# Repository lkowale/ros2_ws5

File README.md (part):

# ros2_ws5

## Sliding toolbar — software

All toolbar code lives here (ros2_ws5). It runs in the Gazebo sim and, for testing,
on the physical **solbot4** robot (pd600) as an overlay on `~/ros2_ws4`. Do not copy
it into ros2_ws4; change it here and redeploy.

| Package | What |
|---|---|
| `toolbar` | `toolbar_service`: executes toolbar moves, enforces soft limits, monitors the actuator, reports to PauseManager. `firmware` param: `solbot_main` (solbot5 board, metres) or `main_esp32_pio` (solbot4 board, ADC counts). Config: `config/toolbar_solbot5.yaml` |
| `toolbar_msgs` | `ToolbarState.msg` (`/toolbar/state`, 10 Hz), `ToolbarControl.srv` (`/toolbar_control`) |
| `solbot4_toolbar` | solbot4 launch (`core_toolbar.launch.py` = ws4 `pd600_core.launch.py` + `toolbar_service`) and calibration (`config/toolbar.yaml`) |
| `tool_slider` | `tool_slider_controller` (row offset → `/tool_bar_position_cmd`, PID), sim actuator + plant-row sim |
| `crop_row_vision` | camera crop-row detection → `/plant_row_offset` |

Interface (metres from centre, +right): `toolbar_service` follows `/tool_bar_position_cmd`
in `auto` mode and publishes the measured `/tool_bar_position`, the same topics
`tool_actuator_sim` uses in the sim. Commands: `set_position`, `center`, `hold`, `auto`,
`enable`, `disable`, `reset_fault`, `get_status` (service `/toolbar_control` or
topic `/toolbar/cmd`). Starts **monitor only** (`actuator_enabled: false`). A disabled
toolbar never pauses the robot.

### Running on solbot4 from the laptop

```bash
bash pd600.sh deploy                # rsync toolbar packages to pd600:~/ros2_ws5, build there on ws4
bash pd600.sh start_bar             # all-in-one: core + toolbar + OAK-D + bar_follower (one tmux)
bash pd600.sh start                 # core stack (run_core_um982.sh, field_nav_hw params) + toolbar, tmux "solbot4"
bash pd600.sh attach                # watch (Ctrl-b d detach, Ctrl-c stop)
bash pd600.sh state                 # one /toolbar/state (raw_position = TPS counts)
bash pd600.sh toolbar enable        # set_position 0.02 | center | hold | auto | reset_fault | disable
bash pd600.sh stop | status
bash pd600.sh ros2 <args...>        # any ros2 command on the robot
bash pd600.sh camera                # OAK-D (solbot4_toolbar/oakd.launch.py, RGB 1280x720 @10 fps) + JPEG
                                    #   domain_bridge 0→1 to hp-zbook, tmux "oakd"; start AFTER `start`
bash pd600.sh view                  # laptop: oakd_view.py (OpenCV window, Hz/kB overlay) of /oakd/rgb/image_raw/compressed, domain 1
bash pd600.sh camera_stop
bash pd600.sh gui                   # laptop: toolbar_gui.py — slider (target sent on release), Enable/Disable/
                                    #   Centre/Auto/Reset fault/HOLD, live state; ssh pipe to toolbar_gui_remote.py, no DDS
```

Requirements on pd600: `~/ros2_ws4` on branch `feature/toolbar-service` (adds the
`CORE_PKG` / `CORE_LAUNCH` / `OVERLAY_SETUP` hook to `run_core_um982.sh`).
`pd600:~/ros2_ws5` is build-only: `deploy` overwrites it, and the deployed version is in `DEPLOYED`.

Gotchas:
- ws4's `run_core*.sh` begin with `pkill -9 -f "ros2|..."`, which kills **any** process with "ros2" in its
  command line, `ros2_ws5` paths included. `pd600.sh start` avoids this. If you start by hand, use
  `cd ~/ros2_ws5 && bash run_solbot4_toolbar.sh` from an interactive shell.
- After removing messages from a rosidl package, rebuild it clean (`rm -rf build/<pkg> install/<pkg>`),
  otherwise typesupport fails to import.
- solbot4 firmware (`main_esp32_pio`) has no goal clamp and no stall, overcurrent or comm-timeout
  protection. The node's limits and jam check are the only guard.

### Status / TODO
- [ ] solbot_main v2 rev C (5 V sensors, ADS1115 module on 5 V): review the new routing in KiCad, check
  Q5/Q6/C24/R35/R40 in JLC's placement preview, order. Confirm the module pin order matches the board labels.

- [x] pd600 ESP32 (`ESP32_solbot_main`, DHCP on `solap`: was .101/.104/.102, **192.168.0.106** on 2026-11-11) runs
  `main_esp32_pio` ws4 (uncommitted: PV hold + per-target drive timer + toolbar min PWM 100), OTA-flashed 2026-11-11.
  The laptop can't reach it; build here, relay through pd600 and resolve the IP there:
  `pio run -e esp32dev_ota` (in `~/ros2_ws4/embedded/main_esp32_pio`), `scp .pio/build/esp32dev_ota/firmware.bin
  ~/.platformio/packages/framework-arduinoespressif32/tools/espota.py pd600:/tmp/`, then
  `ssh pd600 'python3 /tmp/espota.py -i $(getent hosts ESP32_solbot_main.local | cut -d" " -f1) -f /tmp/firmware.bin'`
- [x] Firmware safeguards in `main_esp32_pio` (ws4): toolbar idle until the first `toolbar/set_position`, stall
  (1.5 s, ≤3 counts) and max-drive-time (20 s) trips, `TPS_fault` / `TPS_active` in `ads`. Built, host unit-tested.
  - [x] goal clamp 370..1280 (~4 mm inside the ends), max drive 10 s. OTA-flashed 2026-11-05
- [x] Actuator moves (2nd test 2026-11-05; 1st test had no movement and tripped stall)
- [x] PV SSR 60 s min on/off hold + 42 V hard cut-off in `main_esp32_pio`: OTA-flashed 2026-11-07
  - [ ] commit in ws4; compare the next day's `~/ros2_ws4/logs/pv_ssr/` with 2026-11-07 (up to 58 switches/h)
- [x] Toolbar max-drive timeout (10 s) now counts per target: a goal change > 3 counts restarts it (stall check
  unchanged). OTA-flashed 2026-11-07 together with the PV hold
- [ ] Node: on a firmware-reported fault, `_latch` sends a hold goal, which re-arms the firmware (`TPS_active` true).
  It should leave the firmware idle
- [x] Direction correct, no change needed (`CW`): +right → TPS falls, −left → TPS rises. Both IBT-2 inputs work
- [x] Calibrated: TPS **1300 far left, 350 far right**, toolbar travel **±0.10 m** (200 mm; actuator stroke
  100 mm at 15 mm/s, full stroke ~6.7 s) → 4.75 counts/mm, counts fall going right. Centre 825 counts
- [x] Wire the actuator, `toolbar enable` (holds at the current position, clamped into 370..1280), small `set_position` moves
- [x] IBT-2 pins: GPIO26 RPWM / GPIO27 LPWM (confirmed 2026-11-05)
- [ ] **IMPORTANT — motion interlock:** lift **down** → toolbar may only move while the robot is moving
  (tool in the soil, sliding sideways while stationary would gouge/strain it); lift **up** → always allowed.
  Needs lift state + robot speed in the node (and ideally a firmware-side guard too)
- [x] Laptop slider GUI (`bash pd600.sh gui`)
- [ ] Phone slider via HiveMQ (`outer/toolbar_pos`, `toolbar_outer_bridge`) — running on pd600, get_status round trip via HiveMQ OK; slider move not yet tested
- [ ] Vision loop on solbot4: deploy `tool_slider` + `crop_row_vision` (`PKGS=... bash pd600.sh deploy`), camera topic on solbot4

## Tool slider actuator — IBT-2 on the old main ESP32 board

The sliding toolbar actuator is driven by an IBT-2 (BTS7960) plugged into one of
the spare IBT-2 ports on the old classic-ESP32 main board.

Sources:
- Old wheel firmware (defines the IBT-2 ports): `~/tmp/solbot_arduino/solbot2-2x12vwipersmotors/esp32_master____wheels_diff*`
- Firmware currently on the board: `~/ros2_ws4/embedded/main_esp32_pio` (earlier `main_esp32`)

### Old IBT-2 ports vs current pin usage

| Port (solbot2)   | RPWM | LPWM | Current use (main_esp32_pio)                         |
|------------------|------|------|------------------------------------------------------|
| Front-left wheel | 32   | 33   | taken: steering_act (LEDC ch 0/1)                    |
| Front-right wheel| 25   | 26   | 25 taken: `PV_SWITCH_PIN`; **26 = toolbar RPWM**     |
| Rear-left wheel  | 23   | 22   | 22 taken: I2C SCL (BNO08x + ADS1115, default Wire)   |
| Rear-right wheel | 27   | 13   | **27 = toolbar LPWM**; 13 free                       |
| Lifter           | 19   | 21   | 21 taken: I2C SDA                                    |
| Planter          | 18   | 17   | taken: lift_act (LEDC ch 2/3)                        |
| LAS analog in    | 35   | –    | free (input-only ADC)                                |

Also in use: GPIO34 = steering pot ADC.

### Assignment for the slider

Used (confirmed 2026-11-05), as in ws4 `main_esp32_pio` since `ee2e8b7`:

- RPWM = **GPIO26**, LPWM = **GPIO27**. Neither is a strapping pin.
- LEDC channels **4 / 5** (5 kHz, 8-bit, same as `IBT_2.cpp`)
- Position sensor (TPS): **ADS1115 AIN2** (`TOOLBAR_ADS_CH 2`), published as `TPS` in the `ads` topic

```cpp
#define TOOLBAR_RPWM_PIN 26
#define TOOLBAR_LPWM_PIN 27
#define TOOLBAR_ADS_CH   2
toolbar_act.begin(0, "toolbar_act", TOOLBAR_RPWM_PIN, TOOLBAR_LPWM_PIN, 4, 5, Lin_act_pid::CW);
```

(An earlier plan used RPWM 27 / LPWM 13, the old rear-right wheel port. Not used.)

## WAS (wheel angle sensor) — salvaged BMW position sensor

Under test (2026-10-30) on an ESP32 DevKit V1. Range is about 90°.

| Sensor pin | Function |
|------------|----------|
| 1          | GND      |
| 4          | Signal   |
| 5          | +5 V     |

Pins 2 and 3: unknown / not used.

The sensor runs on 5 V, so its output may go above 3.3 V. Measure the signal
range with a meter before connecting it to an ESP32 ADC pin, and use a divider
(e.g. 10k/20k) if it exceeds ~3.1 V.

## Changelog

Newest first. Toolbar and solbot4-test work. Add an entry with every change.

### 2026-11-11
- **bar_follower `reference: markers` (new default): two knives, one each side of the crop row, each with a
  yellow marker; keep the red bar midway between the markers.** Visual servo on the image, no knife model:
  markers (yellow H 18-45, S>50, V>130, compact 400-4000 px blobs, rows of the measuring tape rejected) ->
  midpoint; bar centreline at the markers' row; `err = u_bar + center_offset_mm·2.62 - u_mid`. Only after the
  toolbar reached its target and was still `settle_s` 0.6 s: median of `settle_frames` 3 errors, if over
  `deadband_mm` (now 3) -> `target = p + err / gain(p)`, gain = `px_per_m + 2·px_per_m2·p` (new `px_per_m2`
  −2867 from the 11-10 sweep). Joint play / scale errors are taken out by the next iteration. One marker
  hidden: the other ± the remembered spacing. Markers or bar lost 0.5 s -> stop commanding (service holds).
  Clamped to the service limits (asymmetric since the zero move). `reference: model` keeps the 11-07 mode.
- Bar detection: tallest red component + pieces on its line (was: all red pieces merged), `red_v_min` 40 -> 75,
  and in markers mode only columns within one marker spacing of the knives. The rusty frame at the left image
  edge (V 43-62) was passing as the bar (u ≈ 18 px).
- Live test markers mode: bar 9 mm off -> −0.8 mm in 2 moves; chasing the bar to the left end the target hit
  −77.4 mm, but the firmware clamps goals at TPS 1280 (−75.2 mm), so the toolbar stayed "moving" until
  `arrive_timeout_s`. Follower clamp now 5 mm inside the service limits (was 2). After the fix: reversal from
  the left end +27 -> +17.6 (joint play ate half the first step) -> +4.1 -> +0.6 mm.
- **bar_follower `reference: knives` (new default): the knives themselves at ground level, not the markers.**
  The yellow markers sit 5-10 cm above the ground, and their parallax put the "centred" bar 22 mm off the
  knives' real midpoint. Inner wing tip of each knife = extreme of the blue-steel mask on its side of the bar
  centreline (left knife max u+v, right knife max v-u, mean of the 30 most extreme px), rows from the tape
  top down ignored (tape and the shank bolt look bluish), blobs < `knife_min_blob_px` 1500 ignored (a bluish
  dirt spot next to the left tip was taken as the tip now and then, error jumping ~6 mm), tips = median of
  the last 3 frames. Stationary noise: sd 1.8 mm with outliers to −6 -> 0.28 mm, range 0.3-1.7 mm.
- Continuous servo hysteresis: start correcting above `deadband_mm` (3), stop updating the target below
  `release_frac`·deadband (1.5 mm) or when at rest inside the deadband. Without it the loop dithered back and
  forth through the implement joint play (near the target small actuator moves don't move the knives).
  After both fixes: target unchanged for 18 s with a still bar, error 0.1-0.3 mm.
- **bar_follower `servo: continuous` (new default for markers mode):** the stepped loop (move, wait for the
  target + 0.6 s + 3 frames, measure, move) made the toolbar visibly stop-and-go behind a moving bar. Now every
  frame: `target = p(t_image) + servo_gain(0.8) * err / gain(p)`, `p(t_image)` interpolated from the
  /toolbar/state history at the image header stamp (pd600 clock), resent only when it changes > 0.5 mm; held
  when still and |err| <= deadband. `servo: stepped` keeps the old loop. Live: 44-50 mm bar moves followed in one
  smooth motion, converged −0.4..+0.8 mm in 2.7-9.3 s, no stalls.
- **Firmware `TOOLBAR_MIN_PWM` 100 (ws4 `main_esp32_pio`, uncommitted, OTA-flashed 2026-11-11 to .106):**
  `Lin_act_pid::min_pwm` (default 40, steering/lift unchanged) is the bottom of `calculate_pwm`'s 5..100-count
  ramp. A 3.5 mm (17-count) follower step got PWM ~75/255, didn't move with the knives on concrete, and tripped
  `stall` after 1.5 s (latched until reset_fault + auto). After the flash: four 3 mm (12-count) steps both ways
  reached the target, no stall.
- pd600 rebooted again 2026-11-11 and the OAK-D was missing from `lsusb` until replugged (same as 11-10).

### 2026-11-10
- **Toolbar zero re-referenced to the bar's working centre (TPS 923, was 825 = mid-stroke).**
  `config/toolbar.yaml`: same counts at the ends (1300 left, 350 right, 4.75 counts/mm), limits now
  `min_position -0.0794` / `max_position +0.1206`; `center` command and 0 m go to TPS 923. Verified on
  pd600 after deploy + restart: raw 923 reads 0.000 m. toolbar_gui picks the new limits up from `/toolbar/state`.
- **`toolbar_cam.yaml` u0 1071.7 -> 1011.7** for the new zero (u0 − 2907·0.0206). Camera check of the sweep:
  max left (raw 1277) knife ≈800 px vs 815 predicted, back to centre ≈1035 vs 1032. Against the tape the knife moves
  ~1.1–1.18 mm per configured TPS mm (−88 mm at −74.6, +66 at +60.8), consistent with the 11-07 px_per_m (1.11).
- Bar-follower test re-run with `start_bar`: bar at u 788 px, follower live (enable, auto, dry_run false) settled
  at −0.056 m with err −0.7 mm.
- **Follower accuracy sweep** (`measure_knife_bar.py` on pd600: after each settle, knife bottom-left corner
  (blue-steel mask; the 11-07 V<95 mask misses the lit wing) vs red-bar centreline at that row, 2.62 px/mm;
  data + annotated frames in `docs/toolbar_cam_calib/follow_check_2026-11-10/`). Goal offset 30 mm, 13 steps:
  arriving from the right (−p) 29.3–31.7 mm; arriving from the left (+p) 27.3 mm at −46 mm, 24–26 mm around
  0, 21.5 at +43, 14.5 at +90 (+94.5 saturated at `limit_m`). The follower's own err stayed within ±2 mm, so the
  error is the camera model. Fit of knife u vs p (new frame): linear `999 + 2644·p ± 39/2` leaves 6.4 px rms
  (10 px max, curved residuals); quadratic `1009.6 + 2788·p − 2867·p² − 47.8/2·dir` leaves 2.3 px rms (3.8 max,
  < 1.5 mm). Local scale falls from 3130 px/m at −0.06 to 2270 at +0.09 (lens edge + linkage).
  The 11-07 linear model (2907 px/m) was fitted on −0.10…−0.01 m (new frame) only. TODO: quadratic in bar_follower.
- OAK-D on pd600 enumerated at 5 Gbps (USB SPEED: SUPER) on bus 2 port 10. pd600 rebooted once
  unexpectedly with the camera attached: watch for a USB power brown-out.

### 2026-11-09
- **solbot_main v2 rev C: 5 V position sensors and an optional ADS1115 module on 5 V, as on the ws4 toolbar.**
  Hall sensors: POS terminal pin 1 = +5V through a 0 R link (direct, as ws4). The output goes to the ESP ADC through 100k/150k (×0.6, 5 V → 3.0 V) + 100 n +
  BAV99. The ADS1115 breakout module sits in a 1x10 socket (J15), lying flat below the SPARE IDC. It is powered from
  +5V and reads the raw 0..5 V wipers (PGA ±6.144 V, I2C 0x48); SDA/SCL pass 2× 2N7002 level shifters (Q5/Q6) so its
  5 V pull-ups don't reach the ESP. R35/R40 moved above the TURN terminal (their old spots were boxed in).
  Routing: rev B copper locked; segments on re-netted pads dropped, dead stubs pruned (`gen_pcb.py`), new connections
  by FreeRouting (pass4) + `gen/route_net.py` (pass5, 2 nets). Only the nets this change touches differ from rev B.
  DRC: 0 unconnected, no clearance errors. Production: BOM 27 lines (new Basic 0 R C21189, 150k C22807; 1M gone),
  99 placed parts. Firmware: `pot_mv` = sensor supply (default 5000, NVS key `pot_mv5`), ESP reading ÷ `pins::POS_DIV`,
  ADS gain ±6.144 V, ADS auto-detect with fallback to the ESP ADC (`settings {"pos_adc":"auto|esp|ads"}`), channel map
  `pins::ADS_CH`. Builds and the host tests pass; not run on hardware.
- **solbot_main v2 firmware (solbot5): ported the ws4 toolbar and PV changes.** The slider (act 3) now starts idle
  until the first `slider/set_position`. It trips `timeout` after 10 s driving towards one target; a goal change of more
  than `stall_delta` restarts that clock. Soft limits come from the solbot4 measurements (counts 370..1280 = ±0.0958 m;
  calibrate on solbot5). PV: 60 s minimum on and off hold, 42 V immediate cut-off in any mode. `ads` adds `TBS_pwm`,
  `TBS_fault`, `TBS_active`; `act/state` adds `active`. Payloads that aren't JSON are ignored (they used to read as goal 0).
  Host tests extended, all pass; firmware builds. Not run on hardware (board not built yet).
- **Removed `embedded/solbot_main` (v1 board)**; v2 is the only solbot5 controller. v1 is in git history before this commit.

### 2026-11-07
- **Firmware: toolbar timeout per target** (ws4 `Lin_act_pid::command()`, flashed with the PV hold change). The
  follower tripped `ESP32 reports toolbar actuator timeout` at 13:28: the target kept moving with the bar, the motor
  never stopped, and the 10 s continuous-drive limit ran out. Now a new goal (> `stall_delta` = 3 counts, so the
  node's periodic resends don't count) restarts the 10 s clock; the stall reference is not reset, so a jammed
  actuator still trips after 1.5 s. After the flash: reset_fault / enable / auto, follower at target (−0.7 mm).
  OTA: the ESP32 had moved to 192.168.0.102 (DHCP); resolve `ESP32_solbot_main.local` on pd600.
- **PV SSR hold (firmware, not flashed):** `main_esp32_pio` (ws4) PV switch keeps each state >= 60 s
  (`PV_MIN_HOLD_MS`) and still cuts PV at once above 42 V (`PV_HARD_OFF_VOLTAGE`). Reason: on 2026-11-07, with the
  41/40 V thresholds, PV switched up to 58 times an hour, with 1-3 s bounces after reconnects.
- **One-session startup for the bar-follower test:** `bash pd600.sh start_bar [launch args]` ->
  `run_solbot4_bar_follower.sh` -> ws4 `run_core_um982.sh` with `CORE_LAUNCH=core_bar_follower.launch.py`
  (`solbot4_toolbar/launch/`): core_toolbar (pd600_core + toolbar_service + toolbar_outer_bridge) + OAK-D +
  camera domain_bridge (`CAMERA_BRIDGE_CYCLONEDDS_URI`) + bar_follower. Args `use_camera`, `use_bar_follower`,
  `camera_model`, `bar_follower_params`. Replaces `start` + `camera` + `follow` (start_bar refuses if those
  sessions run); `stop` handles both launches. Toolbar still starts disabled, follower in dry_run.
- **`bar_follower`** (`solbot4_toolbar/scripts/bar_follower.py`, params in `config/toolbar_cam.yaml`): keeps the knife's
  left edge `offset_mm` (30) right of a red bar/cable. Red mask -> per-row edge midpoints -> line fit -> bar column at
  v_ref; target `p = (u_bar + offset·2.62 px/mm - u0 ∓ hysteresis/2) / px_per_m`, approach-direction aware, 5 mm
  deadband, published on `/tool_bar_position_cmd` (no PID: the camera is frame-fixed, the firmware closes the loop).
  Bar lost 0.5 s -> stops publishing, `toolbar_service` holds. Starts `dry_run: true`. Status JSON
  `/bar_follower/status`, overlay `/bar_follower/image/compressed` (bridged to the laptop).
  `pd600.sh follow | follow_stop | follow_view`, `view [topic]`. Static check: bar 795 px, toolbar −0.0236 ->
  target −0.075 m; the TPS prediction matched the detected knife corner within 7 px (~3 mm).
- **OAK-D <-> toolbar calibration** (`solbot4_toolbar/config/toolbar_cam.yaml`, data and frames in
  `docs/toolbar_cam_calib/`): lift down, tape on the floor, toolbar swept ±0.08 m, knife bottom-left corner
  auto-detected. `u_impl = 1071.7 + 2907·p ± 20 px` (px, p in m, +p = image right; knife visible only for p <= ~+0.01).
  Ground scale 26.2 px/cm, so the knife moves 1.11 mm per TPS mm (TPS travel scale or knife pivoting).
  **Hysteresis ~40 px = ~15 mm** between approach directions (repeatable to 1 px per direction): implement joint play.
- `toolbar_gui.py` + `toolbar_gui_remote.py`, `bash pd600.sh gui`: tkinter slider GUI on the laptop. The robot graph is
  loopback-only, so the GUI copies `toolbar_gui_remote.py` to pd600 and runs it over ssh (JSON lines: `/toolbar/state`
  out, `/toolbar_control` requests in). Slider sends `set_position` on release; ←/→ ±5 mm (Shift ±1 mm), `c` centre,
  space HOLD; closing the window sends hold if enabled. `deploy` also copies the remote helper.
- `toolbar_outer_bridge` (package `toolbar`, started by `core_toolbar.launch.py`): phone MQTT app via the HiveMQ cloud
  broker, same pattern as ws4 `mqtt_op` outer/steer + outer/speed. `outer/toolbar_pos` `{"data": mm}` (−100..100,
  +right) → `toolbar_control set_position`; `outer/toolbar_cmd` `{"data": "enable"|"center"|"hold"|…}`; replies on
  `outer/toolbar_state` `{pos_mm, target_mm, state, ok, message}`. Coalesces slider bursts (newest value, one call in flight).

### 2026-11-06
- OAK-D on solbot4: `solbot4_toolbar/launch/oakd.launch.py` + `config/oakd.yaml` (depthai_ros_driver, RGB only,
  720p 10 fps, `CAMERA_MODEL` default OAK-D-LITE), `config/camera_bridge.yaml`, `run_solbot4_camera.sh`;
  `pd600.sh camera | camera_stop | view`. `pd600.sh stop` now waits for `core_toolbar.launch.py` only.
  First run: OAK-D-LITE (MXID 19443010A18FDC7D00) on the pd600 front USB-C, USB3 SUPER_PLUS after a replug
  (first plug-in: no Type-C partner detected). 10 Hz on pd600, only ~3 Hz arriving on hp-zbook over Tailscale.
  Replugging re-enumerated the UM982 CH340 (`/dev/um982` → ttyUSB1); GPS kept running.
  JPEG q95 (426 kB frames, ~4 MB/s) saturated the solap WiFi once the laptop joined it (LAN ping 460 ms, viewer
  stalled): `oakd.yaml` sets jpeg_quality 50 (~140 kB, ping 1.5 ms, 8 Hz on the laptop), bridge image QoS best effort.
  `view` runs `oakd_view.py` (rqt_image_view / image_view never subscribed to the bridged compressed topic), under `env -i` (rqt crashed in the VS Code snap shell: GLib-GIO settings schema).
- OAK-D ground footprint (1280x720, fx 912), tape measures on flat concrete:

  | Lift | Camera height (measured) | Ground window | Scale | Optical-equivalent height |
  |---|---|---|---|---|
  | down | 44 cm | 55 × 31 cm, rectangular | 23.2 px/cm (0.43 mm/px), uniform | ~39 cm |
  | up | 64 cm | ~79 × 50 cm, trapezoid | 17.8 (top) → 15.5 (mid) → 12.5 (bottom) px/cm | ~59 cm |

  Lift up the camera pitches (bottom of the image looks farther away) and the lift frame hides the right ~15 %.
  The measured heights are ~5 cm above the optical-equivalent height (measured to the mount, not the lens).
  Lift down is a clean nadir view; lift up needs a tilt/homography correction before metric use.
  Frames: `docs/oakd_ground/lift_down_44cm.jpg`, `docs/oakd_ground/lift_up_64cm.jpg`.
- TODO added: toolbar motion interlock — lift down ⇒ move only while driving; lift up ⇒ always allowed.

### 2026-11-05
- **Toolbar moves, direction correct** (2nd powered test, standalone node, no robot stack):
  `set_position −0.023` (10 mm right): TPS 983 → 937 in ~0.9 s, goal 934 (3 counts ≈ 0.6 mm off, inside the
  firmware deadband), `at_target`. Back to `−0.033` (10 mm left): TPS 937 → 979 in ~1 s, goal 982. No faults.
  `CW` in firmware is correct.
- **First powered toolbar test** (standalone `toolbar_service` on pd600, no robot stack): enable held at TPS 983
  (−0.033 m). `set_position −0.023` (goal 934) drove PWM ~142 for 1.5 s, but TPS stayed at 982–983. The firmware
  tripped `stall`, the node latched `actuator_fault`. **No movement, so the direction is still unknown.**
  The safeguards worked as designed.
- **Toolbar travel corrected to ±0.10 m** (200 mm toolbar travel from the 100 mm actuator stroke): node limits
  ±0.10 m, 4.75 counts/mm. Firmware clamp and timers are unchanged (counts/seconds), comments only, no reflash.
- **Toolbar calibrated and firmware flashed:** TPS 1300 left / 350 right, actuator 100 mm stroke, 15 mm/s.
  `solbot4_toolbar/config/toolbar.yaml`: ±0.050 m (corrected to ±0.10 m, see above), counts 1300/350,
  tolerances 2 mm and jam 5 mm.
  Firmware: clamp 370..1280, max drive 10 s. OTA-flashed: boots idle (`TPS_active` false, PWM 0). Before the flash,
  the old firmware was again driving PWM 250 (goal 1313, TPS 495, after the toolbar was moved by hand to measure).
  Deployed to pd600.
- **Firmware toolbar safeguards** (ws4 `main_esp32_pio`, `Lin_act_pid::enable_safeguards`, opt-in, so steering and lift
  are unchanged): idle at boot until the first command, goal clamp, stall trip (driving, ≤3 counts of movement in
  1.5 s) and timeout trip (driving > 20 s). Trips stop the motor and set goal := position, and a new
  `toolbar/set_position` re-arms. Null or invalid `data` is ignored, where before it read as goal 0. Motor is stopped
  when exactly on target (the old code kept the previous PWM). `ads` gains `TPS_fault` and `TPS_active`.
  `toolbar_service` latches `TPS_fault` stall/timeout as `actuator_fault`. Not flashed yet: waiting for the
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
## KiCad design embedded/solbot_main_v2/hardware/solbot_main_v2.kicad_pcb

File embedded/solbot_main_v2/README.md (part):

# solbot_main v2 (rev B / rev C) — compact ESP32-S3 main controller, JLCPCB Basic parts

> **rev C (2026-11-09): production files regenerated and checked by script. Two manual checks
> are left before ordering** (see the end of this list).
> * **Hall position sensors on 5 V** (as on the ws4 toolbar): POS terminal pin 1 = +5V through a 0 R
>   link (R35/R40/R45/R50; fit 10–47 R there if you want a shorted cable not to pull +5V down, at the
>   cost of supply volts). The sensor output goes to the ESP ADC through a 100k/150k divider (5 V reads
>   as 3.0 V; an open wiper reads 0) + 100 n + BAV99 clamp. The rev B 1 k from 3V3A and the 1M
>   wiper pull-down are gone. R35/R40 (A1/A2 supply) moved to the free strip above the TURN
>   terminal: their old spots could only be reached through the 3V3A pull-up row.
> * A 1x10 socket (J15, hand-solder) for an optional **ADS1115 breakout module** plugged in flat,
>   **powered from +5V like on ws4** and reading the **raw 0..5 V wipers** (PGA ±6.144 V). SDA/SCL
>   reach it through two 2N7002 level shifters (Q5/Q6, gate 3V3A), so the module's own 10k pull-ups
>   to 5 V never reach the ESP pins. C24 = 100 n on its VDD.
> * Routing: the rev B copper is kept apart from the segments that ended on re-netted pads (dropped)
>   and the dead stubs this left (pruned at the end). Only the nets this change touches differ from
>   rev B. New connections: FreeRouting (`solbot_main_v2_pass4.ses`) + `gen/route_net.py` for the two
>   it couldn't close (`solbot_main_v2_pass5_*.ses`).
> * DRC: 0 unconnected, 0 clearance errors, 0 shorts. The other warnings are the same as rev B, plus
>   headless-only `lib_footprint_issues` for J15/C24/Q5/Q6.
> * `hardware/production/` was regenerated with the Fabrication Toolkit plugin (your saved
>   options). BOM: 27 lines, all with LCSC numbers. New: 0 R (C21189) and 150k (C22807), both Basic;
>   1M is gone; Q5/Q6 joined the 2N7002 line (C8545). Positions: 99 SMD parts. J15 is in neither file.
> * **Still to do by hand:** look over the new routing in KiCad (resistor block, around R35/R40
>   above the TURN terminal, under the ADS socket), and check Q5/Q6/C24/R35/R40 in JLC's placement
>   preview. Order as before: 2-layer, 1 oz. Upload
>   `production/solbot_main_v2.zip`, `production/bom.csv` and `production/positions.csv`.

The ESP32-S3 main controller for solbot5. It replaced v1 (a 190 × 155 mm board with a full
on-board 4-pack power path, removed from the repo 2026-11-09; see git history before that date).
This board has **no battery switching on board**. It

* runs from the robot's **12 V rail**
* **monitors the main battery bus voltage** (10S…20S, up to ~95 V) and its own 12 V rail
* switches **PV on/off through external DC solid-state relays** (2 driver outputs)
* drives **4 IBT-2 (BTS7960)** modules on **2×5 IDC sockets with the v3 pinout**, plus
  current sensing on the previously unused IDC pins 5/6
* reads the **4 position pots directly on the ESP32-S3 ADC1**, plus the **BNO085** on I2C

Board: **120 × 85 mm**, 2 layers, 1 oz is fine.

## JLCPCB assembly (rev B)

Every SMD part was checked on jlcpcb.com on 2026-10-16: **25 Basic lines and 1 Preferred
Extended (SMBJ18A TVS), 0 Extended**, so there are no extended-part fees with Economic
assembly.

**Production files: KiCad → Fabrication Toolkit (JLC plugin)** writes `hardware/production/`
(Gerber/drill zip, `bom.csv`, `positions.csv`). It's been checked against this board:
* Every connector is labelled on the silkscreen: function (TURN / LIFT / SLIDE / SPARE,
  12V IN, BUS SENSE, SSR1/2 PV, E-STOP, IMU) and pins (`+ W -`, `+ -`, `NC`, IMU pin names),
  plus an IBT-2 IDC pin legend at the top right.
* Every SMD footprint has an `LCSC` property (copied from the schematic field), so the
  plugin's BOM has all 26 lines with the right part numbers.
* Hand-soldered through-hole parts (12 V, BUS, SSR, E-stop and pot terminals, the IDC
  sockets, JST-XH, and the DevKit sockets) are "not in BOM" in the schematic and "exclude
  from BOM / position files" on the PCB, so they don't appear in either file.
* Keep the default options ("auto translate" on: rotation fixes for SOT-23/SOT-223/SOIC).
* In JLC's placement preview, check the polarity of D1/D3 (SS34), D2 (TVS) and the LEDs.
  The plugin has no rotation entry for D_SMA/D_SMB/LED footprints. If one is wrong, add an
  `FT Rotation Offset` field (e.g. 180) to that symbol.
* Don't rename the `LCSC` field or add a field called `JLC`/`MPN`: the plugin reads those as
  part numbers.

`hardware/bom_jlc.csv` (from `build.py`) is only a cross-check. Always order with the plugin's
`production/` files.

Changes from rev A that this required (none of the replaced parts is Basic):

| rev A (Extended) | rev B (Basic) |
|---|---|
| AP63205 buck + 4.7 µH inductor | 2× AMS1117-5.0 (logic / ESP32, like v3's 2× 7805), 2×22 Ω pre-drop on the ESP rail |
| AP2112K-3.3 | XC6206P332MR-G |
| ADS1115 | ESP32-S3 ADC1 (GPIO1–10 all used), 16× oversampled; rev B: pot top from 3.3 V through 1 k. Rev C: 5 V sensors, wiper ×0.6 divider, optional ADS1115 module back on a socket |
| 74HCT244 + /OE gate | 2× 74HC14 (inverting → PWM driven active-low, 10 k pull-ups keep it off at boot); E-stop now gates the IBT-2 **R_EN/L_EN** (IDC 3/4) through 2× 2N7002 |
| BAT54S | BAV99 |
| PTC fuse, 47 µF electrolytic | removed (fuse the 12 V feed externally, ≤ 2 A) / 2× 10 µF 1206 |
| 0603 green/yellow LEDs | KT-0805G / KT-0805Y |

Thermal: at about 150 mA the ESP-rail AMS1117 dissipates about 0.7 W (the 22 Ω resistors take
about 0.25 W). Both regulator tabs have copper areas. If the robot has a 5 V rail, the board
could be fed from that instead.

```
solbot_main_v2/
├── hardware/      KiCad 7 project, bom.csv, schematic PDF (production files: JLC plugin)
│   └── gen/       Python generators (design.py = single source of truth)
└── firmware/      PlatformIO, ESP32-S3 (env solbot_main_v2), test/host/run.sh
```

## PV switch with the DELIXI CDG1-1DD/25A SSRs (proposal)

DC SSRs like the CDG1-1DD (input 3–32 V DC, load 12–220 V DC 25 A) have a MOSFET output.
A MOSFET **conducts backwards through its body diode when off**. A single SSR between PV
and the battery therefore either can't stop charging (wired one way), or lets the battery
back-feed the panel at night (wired the other way). With your **two SSRs, wire the outputs
in series back-to-back**:

```
            SSR1 (output)          SSR2 (output)
 PV+ ──fuse──[+ ····· −]────────────[− ····· +]──fuse── BUS+ (battery)
 PV− ─────────────────────────────────────────────────── GND

 board J "SSR1": pin1 +12V → SSR1 input +, pin2 → SSR1 input −
 board J "SSR2": pin1 +12V → SSR2 input +, pin2 → SSR2 input −
 (firmware default: SSR2 mirrors SSR1)
```

* Off: each body diode is blocked by the other SSR, so there's no charging and no night
  back-feed.
* On: two MOSFET channels in series, with no diode drop.
* **Check first:** with an SSR unpowered, use the multimeter diode test across its output.
  If it reads about 0.5 V from − to +, it has the body diode and the back-to-back pair is
  required. If it blocks both ways, one SSR is enough (set SSR2 to manual and use it for
  something else).
* About 10 A (400 W @ 40 V) is fine for 25 A parts, but give them a heatsink plate.
* If you only want to use one SSR: one SSR plus a blocking Schottky
  (e.g. 45 V / 40 A, on a heatsink) also works, at the cost of ~0.5 V of drop.

Charge control is the v3 behaviour, scaled by cell count. At 10S, PV goes **off at
≥ 41.0 V** and **back on below 40.0 V**, with a 30 s minimum off-time. PV is forced off
whenever the bus reading is implausible (sense wire disconnected).

## Hardware

| Block | Notes |
|---|---|
| 12 V in | MKDS 5.08 terminal → SS34 reverse-polarity diode → SMBJ18A TVS (fuse externally) |
| 5 V | 2× AMS1117-5.0: `5V_ESP` (DevKit, via SS34 USB back-feed block) and `+5V` (IBT-2 logic, 74HC14, IMU) |
| 3.3 V | XC6206P332MR → I2C pull-ups, clamps, level-shifter gates (rev B: also pot excitation) |
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
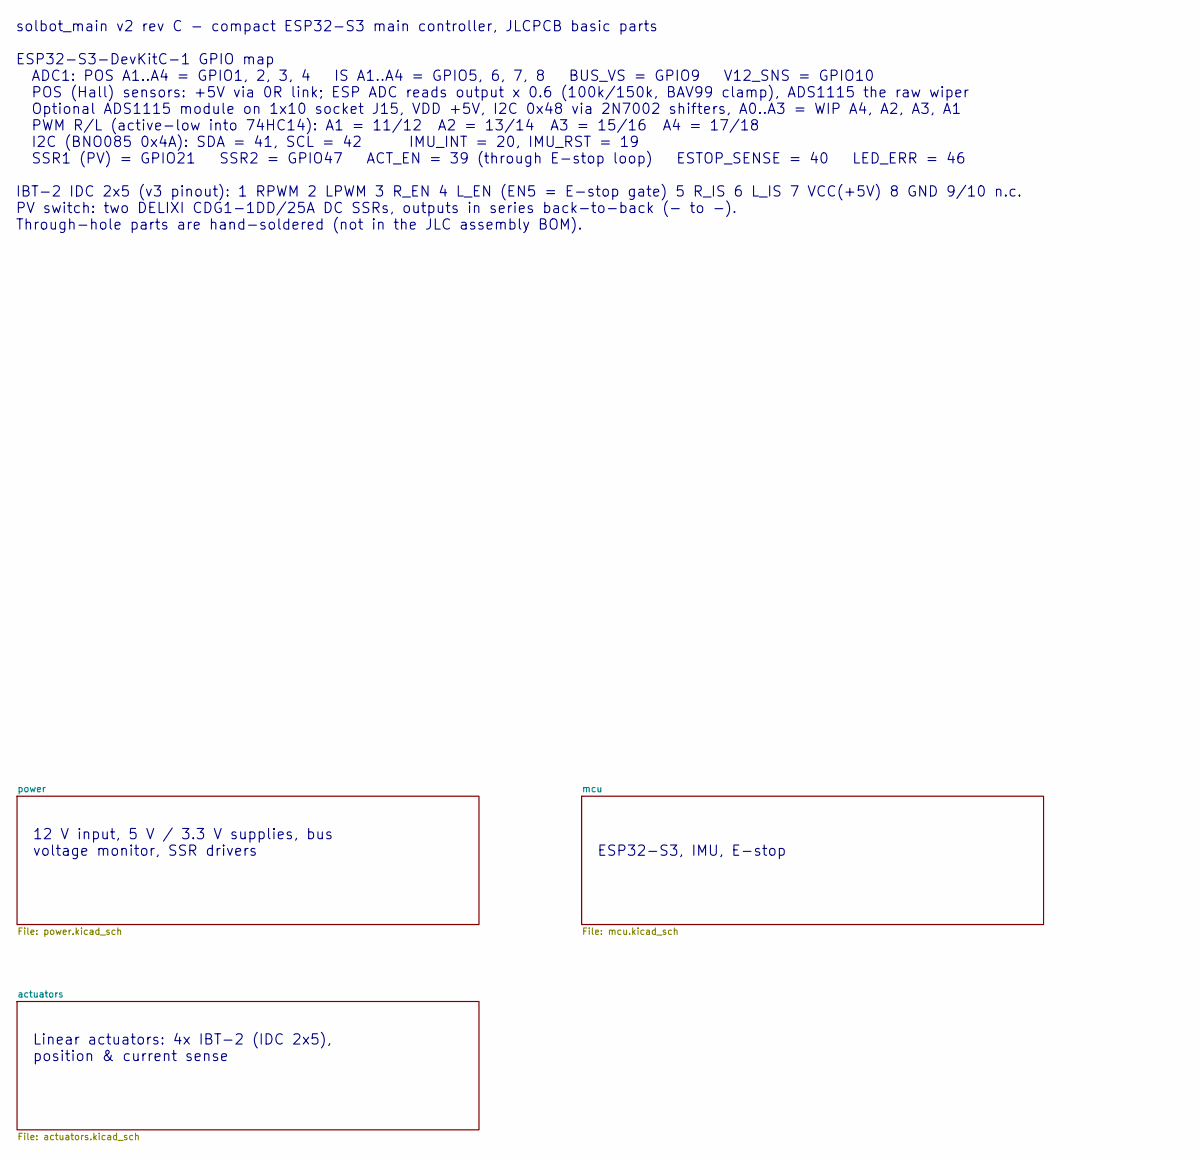
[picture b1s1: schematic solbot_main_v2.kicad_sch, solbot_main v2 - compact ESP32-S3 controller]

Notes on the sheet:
solbot_main v2 rev C - compact ESP32-S3 main controller, JLCPCB basic parts ESP32-S3-DevKitC-1 GPIO map ADC1: POS A1..A4 = GPIO1, 2, 3, 4 IS A1..A4 = GPIO5, 6, 7, 8 BUS_VS = GPIO9 V12_SNS = GPIO10 POS (Hall) sensors: +5V via 0R link; ESP ADC reads output x 0.6 (100k/150k, BAV99 clamp), ADS1115 the 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
12 V input, 5 V / 3.3 V supplies, bus voltage monitor, SSR drivers
ESP32-S3, IMU, E-stop
Linear actuators: 4x IBT-2 (IDC 2x5), position & current sense

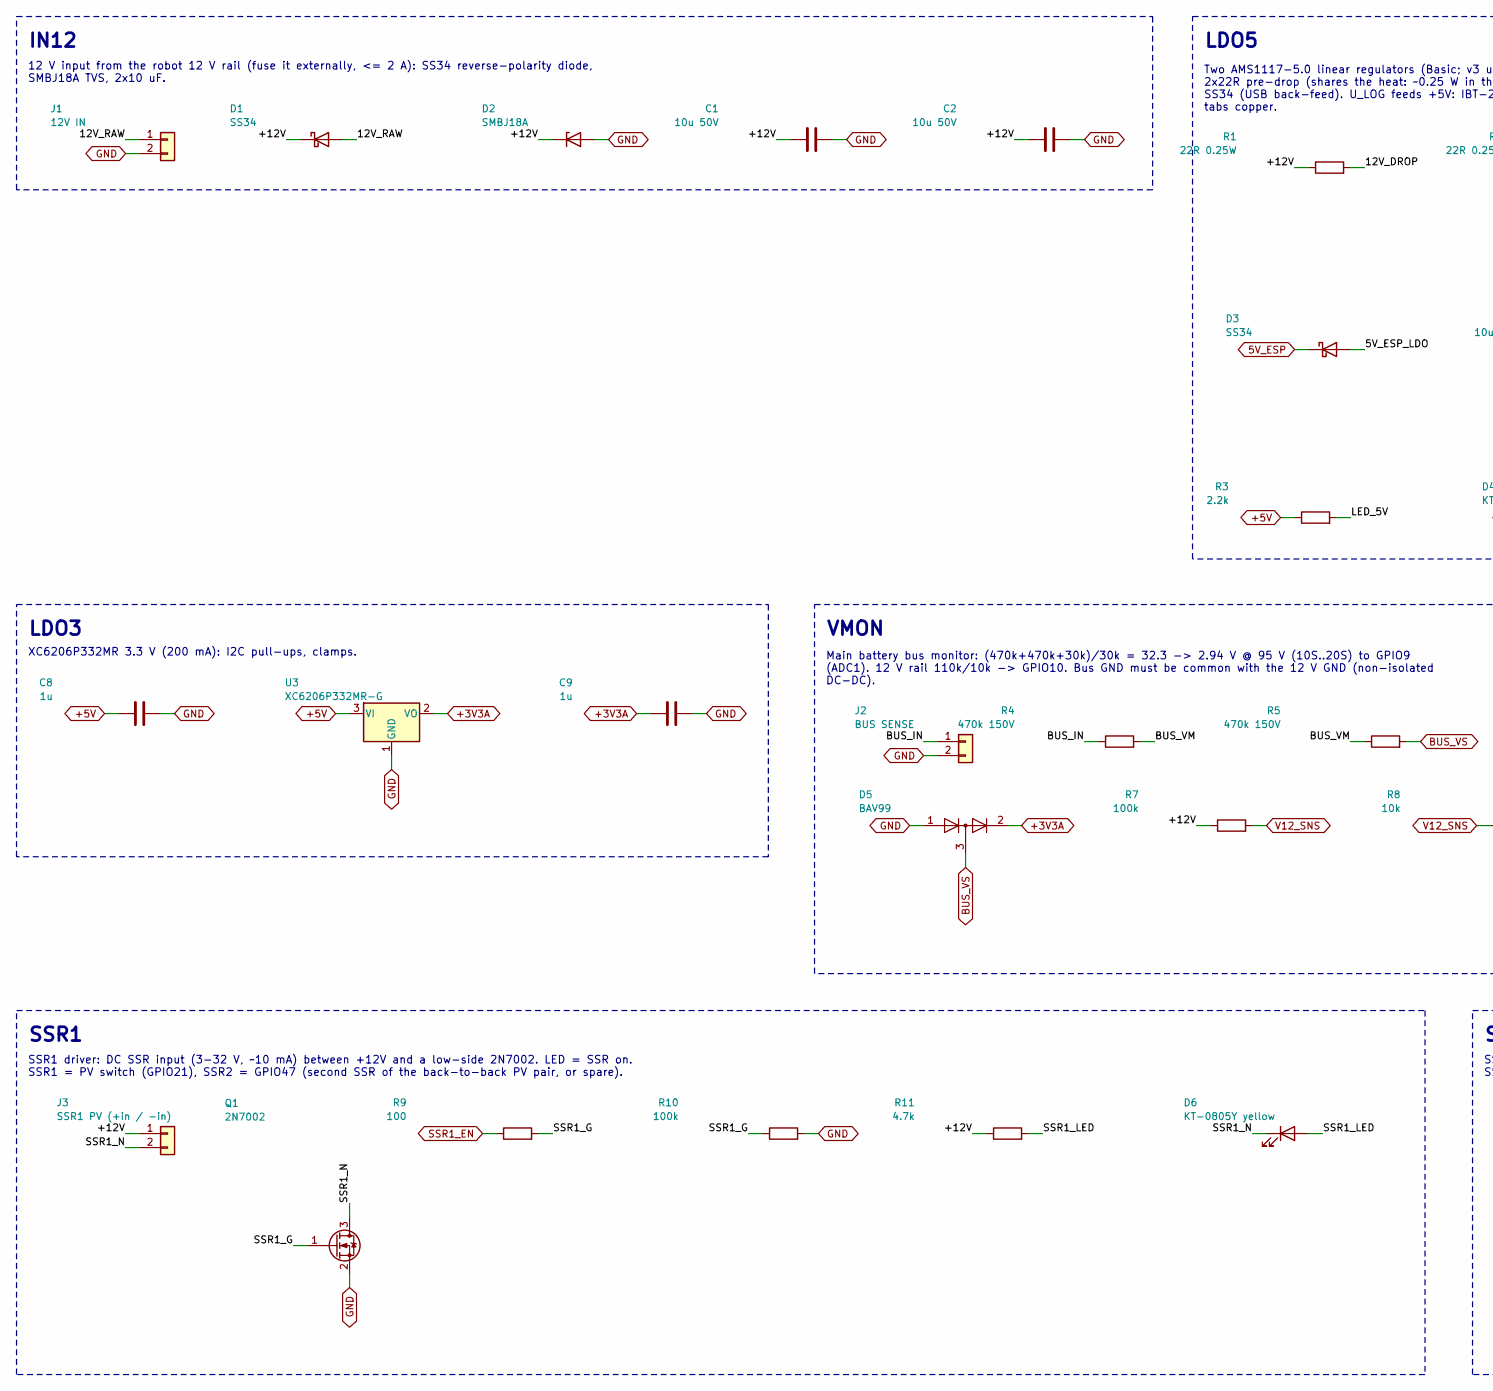
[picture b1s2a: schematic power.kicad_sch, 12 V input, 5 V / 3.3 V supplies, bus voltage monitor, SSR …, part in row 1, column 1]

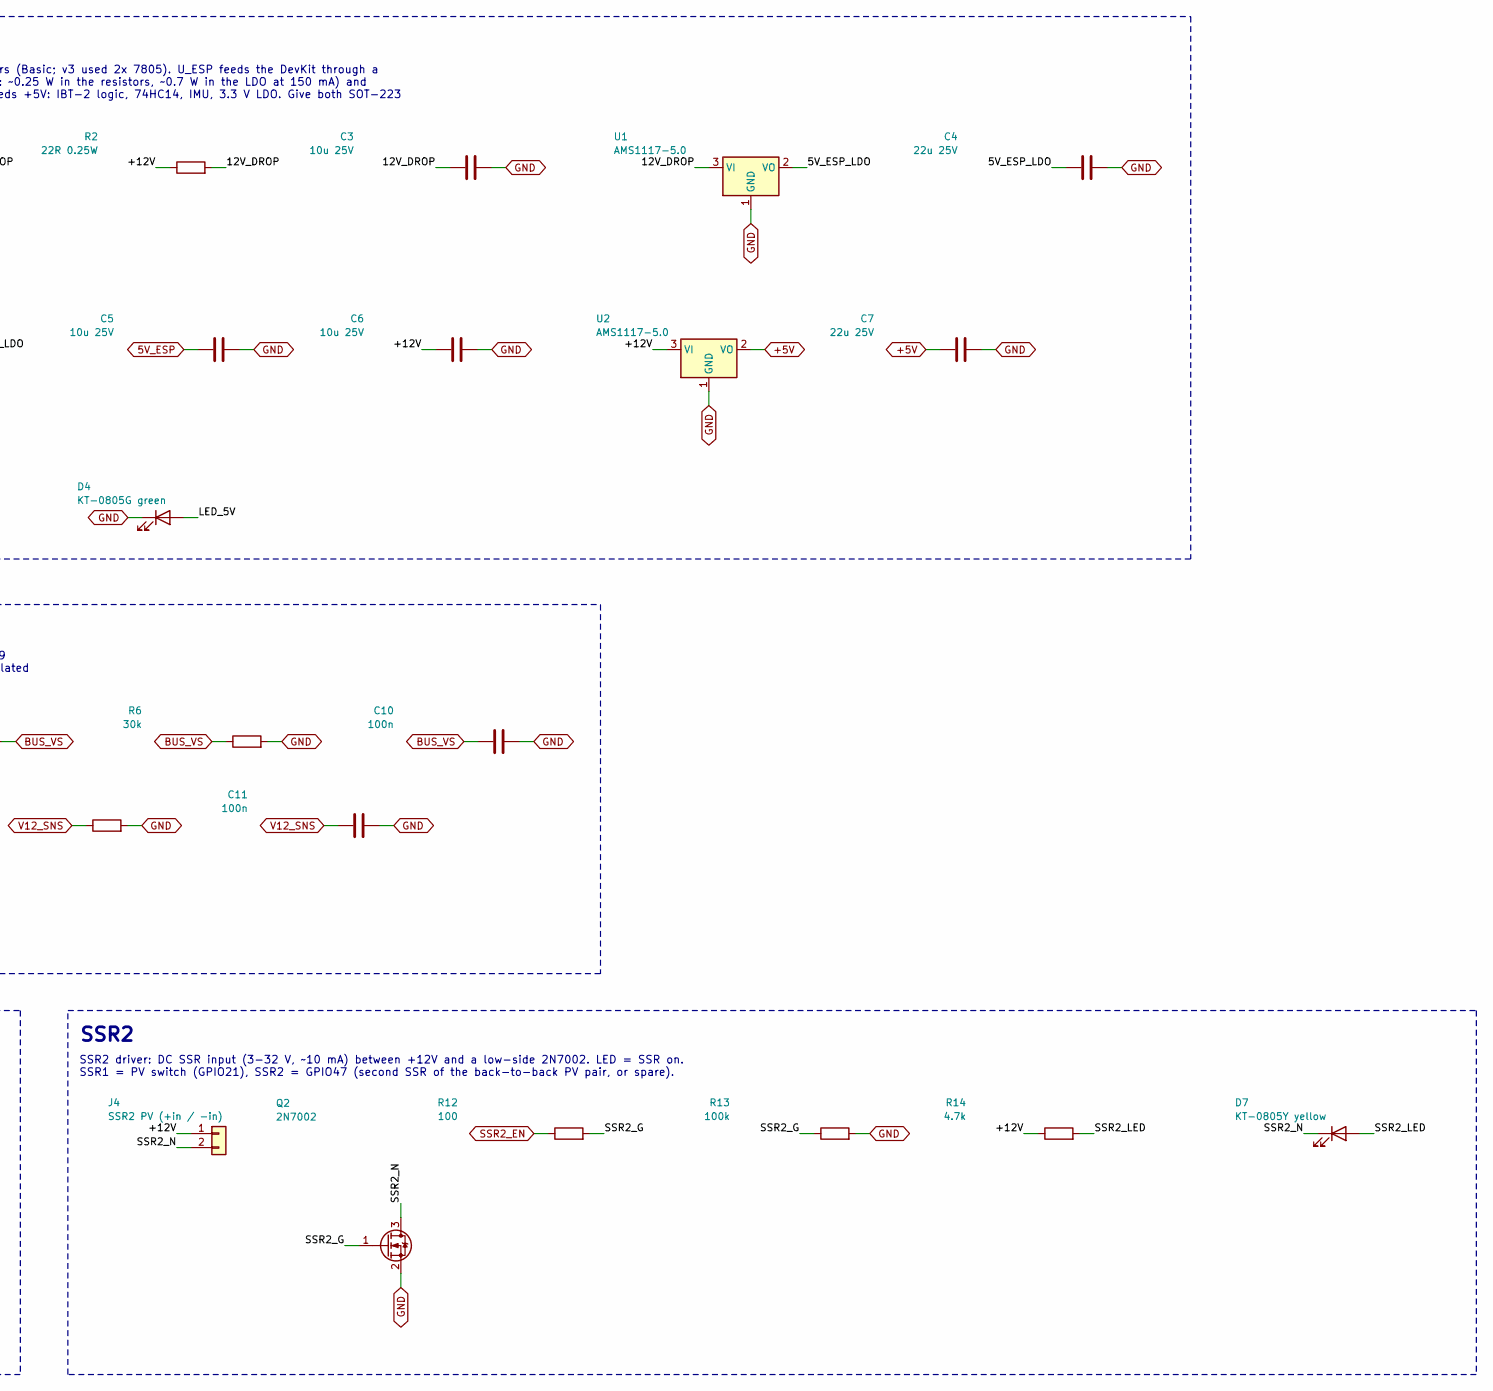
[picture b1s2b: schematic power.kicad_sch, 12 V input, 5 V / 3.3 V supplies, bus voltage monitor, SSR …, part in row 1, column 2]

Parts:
C1, C2: 10u 50V; C_1206_3216Metric; LCSC C13585
C3, C5, C6: 10u 25V; C_0805_2012Metric; LCSC C15850
C4, C7: 22u 25V; C_0805_2012Metric; LCSC C45783
C8, C9: 1u; C_0603_1608Metric; LCSC C15849
C10, C11: 100n; C_0603_1608Metric; LCSC C14663
D1, D3: SS34; D_SMA; LCSC C8678
D2: SMBJ18A; D_SMB; LCSC C19077573
D4: KT-0805G green; LED_0805_2012Metric; LCSC C2297
D5: BAV99; SOT-23; LCSC C2500
D6, D7: KT-0805Y yellow; LED_0805_2012Metric; LCSC C2296
J1: 12V IN; TerminalBlock_Phoenix_MKDS-1,5-2-5.08_1x02_P5.08mm_Horizont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
J2: BUS SENSE; TerminalBlock_Phoenix_PT-1,5-2-3.5-H_1x02_P3.50mm_Horizontal
J3: SSR1 PV (+in / -in); TerminalBlock_Phoenix_PT-1,5-2-3.5-H_1x02_P3.50mm_Horizontal
J4: SSR2 PV (+in / -in); TerminalBlock_Phoenix_PT-1,5-2-3.5-H_1x02_P3.50mm_Horizontal
Q1, Q2: 2N7002; SOT-23; LCSC C8545
R1, R2: 22R 0.25W; R_1206_3216Metric; LCSC C17958
R3: 2.2k; R_0603_1608Metric; LCSC C4190
R4, R5: 470k 150V; R_0805_2012Metric; LCSC C17709
R6: 30k; R_0603_1608Metric; LCSC C22984
R7, R10, R13: 100k; R_0603_1608Metric; LCSC C25803
R8: 10k; R_0603_1608Metric; LCSC C25804
R9, R12: 100; R_0603_1608Metric; LCSC C22775
R11, R14: 4.7k; R_0603_1608Metric; LCSC C23162
U1, U2: AMS1117-5.0; SOT-223-3_TabPin2; LCSC C6187
U3: XC6206P332MR-G; SOT-23-3; LCSC C5446

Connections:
5V_ESP: C5.1, D3.1 (K); also elsewhere on the board
5V_ESP_LDO: C4.1, D3.2 (A), U1.2 (VO)
12V_DROP: C3.1, R1.2, R2.2, U1.3 (VI)
12V_RAW: D1.2 (A), J1.1
+3V3A: C9.1, D5.2 (A), U3.2 (VO); also elsewhere on the board
+5V: C7.1, C8.1, R3.1, U2.2 (VO), U3.3 (VI); also elsewhere on the board
+12V: C1.1, C2.1, C6.1, D1.1 (K), D2.1 (K), J3.1, J4.1, R1.1, R2.1, R7.1, R11.1, R14.1, U2.3 (VI)
BUS_IN: J2.1, R4.1
BUS_VM: R4.2, R5.1
BUS_VS: C10.1, D5.3 (K), R5.2, R6.1; also elsewhere on the board
GND: C1.2, C2.2, C3.2, C4.2, C5.2, C6.2, C7.2, C8.2, C9.2, C10.2, C11.2, D2.2 (A), D4.1 (K), D5.1 (K), J1.2, J2.2, Q1.2 (S), Q2.2 (S), R6.2, R8.2, R10.2, R13.2, U1.1 (GND), U2.1 (GND), U3.1 (GND); also elsewhere on the board
LED_5V: D4.2 (A), R3.2
SSR1_EN: R9.1; also elsewhere on the board
SSR1_G: Q1.1 (G), R9.2, R10.1
SSR1_LED: D6.2 (A), R11.2
SSR1_N: D6.1 (K), J3.2, Q1.3 (D)
SSR2_EN: R12.1; also elsewhere on the board
SSR2_G: Q2.1 (G), R12.2, R13.1
SSR2_LED: D7.2 (A), R14.2
SSR2_N: D7.1 (K), J4.2, Q2.3 (D)
V12_SNS: C11.1, R7.2, R8.1; also elsewhere on the board

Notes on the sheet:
IN12
12 V input from the robot 12 V rail (fuse it externally, <= 2 A): SS34 reverse-polarity diode, SMBJ18A TVS, 2x10 uF.
LDO5
Two AMS1117-5.0 linear regulators (Basic; v3 used 2x 7805). U_ESP feeds the DevKit through a 2x22R pre-drop (shares the heat: ~0.25 W in the resistors, ~0.7 W in the LDO at 150 mA) and SS34 (USB back-feed). U_LOG feeds +5V: IBT-2 logic, 74HC14, IMU, 3.3 V LDO. Give both SOT-223 tabs copper.
LDO3
XC6206P332MR 3.3 V (200 mA): I2C pull-ups, clamps.
VMON
Main battery bus monitor: (470k+470k+30k)/30k = 32.3 -> 2.94 V @ 95 V (10S..20S) to GPIO9 (ADC1). 12 V rail 110k/10k -> GPIO10. Bus GND must be common with the 12 V GND (non-isolated DC-DC).
SSR1
SSR1 driver: DC SSR input (3-32 V, ~10 mA) between +12V and a low-side 2N7002. LED = SSR on. SSR1 = PV switch (GPIO21), SSR2 = GPIO47 (second SSR of the back-to-back PV pair, or spare).
SSR2
SSR2 driver: DC SSR input (3-32 V, ~10 mA) between +12V and a low-side 2N7002. LED = SSR on. SSR1 = PV switch (GPIO21), SSR2 = GPIO47 (second SSR of the back-to-back PV pair, or spare).

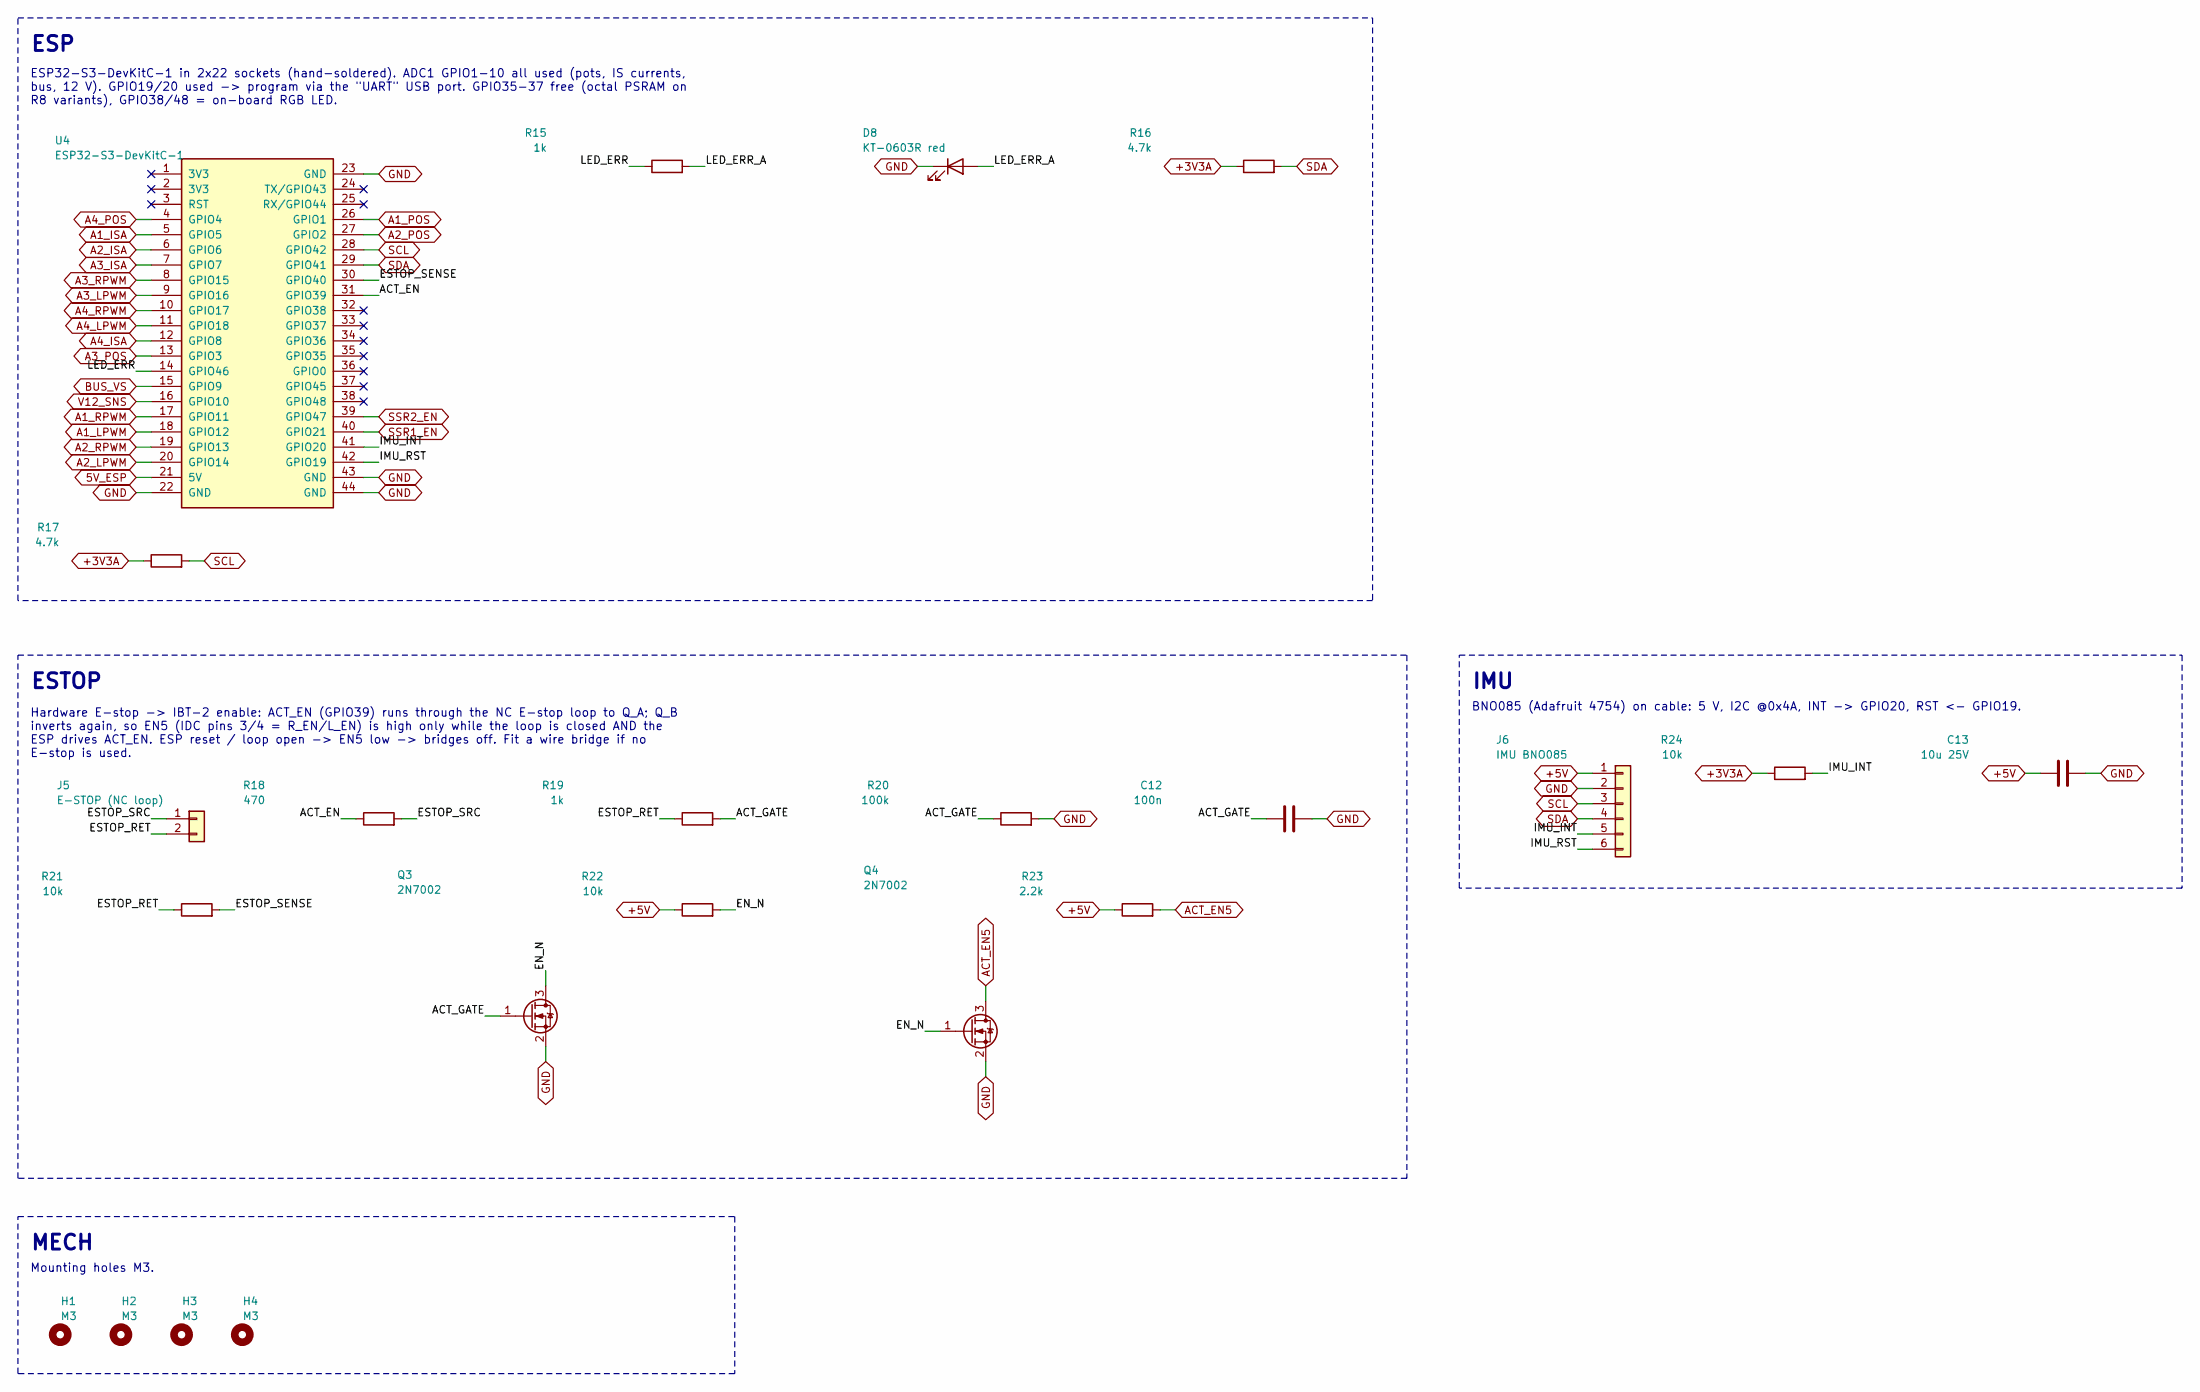
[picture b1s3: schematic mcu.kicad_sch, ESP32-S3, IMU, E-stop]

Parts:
C12: 100n; C_0603_1608Metric; LCSC C14663
C13: 10u 25V; C_0805_2012Metric; LCSC C15850
D8: KT-0603R red; LED_0603_1608Metric; LCSC C2286
H1, H2, H3, H4: M3; MountingHole_3.2mm_M3
J5: E-STOP (NC loop); TerminalBlock_Phoenix_PT-1,5-2-3.5-H_1x02_P3.50mm_Horizontal
J6: IMU BNO085; JST_XH_B6B-XH-A_1x06_P2.50mm_Vertical
Q3, Q4: 2N7002; SOT-23; LCSC C8545
R15, R19: 1k; R_0603_1608Metric; LCSC C21190
R16, R17: 4.7k; R_0603_1608Metric; LCSC C23162
R18: 470; R_0603_1608Metric; LCSC C23179
R20: 100k; R_0603_1608Metric; LCSC C25803
R21, R22, R24: 10k; R_0603_1608Metric; LCSC C25804
R23: 2.2k; R_0603_1608Metric; LCSC C4190
U4: ESP32-S3-DevKitC-1; ESP32-S3-DevKitC-1_Socket

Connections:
5V_ESP: U4.21 (5V); also elsewhere on the board
+3V3A: R16.1, R17.1, R24.1; also elsewhere on the board
+5V: C13.1, J6.1, R22.1, R23.1; also elsewhere on the board
A1_ISA: U4.5 (GPIO5); also elsewhere on the board
A1_LPWM: U4.18 (GPIO12); also elsewhere on the board
A1_POS: U4.26 (GPIO1); also elsewhere on the board
A1_RPWM: U4.17 (GPIO11); also elsewhere on the board
A2_ISA: U4.6 (GPIO6); also elsewhere on the board
A2_LPWM: U4.20 (GPIO14); also elsewhere on the board
A2_POS: U4.27 (GPIO2); also elsewhere on the board
A2_RPWM: U4.19 (GPIO13); also elsewhere on the board
A3_ISA: U4.7 (GPIO7); also elsewhere on the board
A3_LPWM: U4.9 (GPIO16); also elsewhere on the board
A3_POS: U4.13 (GPIO3); also elsewhere on the board
A3_RPWM: U4.8 (GPIO15); also elsewhere on the board
A4_ISA: U4.12 (GPIO8); also elsewhere on the board
A4_LPWM: U4.11 (GPIO18); also elsewhere on the board
A4_POS: U4.4 (GPIO4); also elsewhere on the board
A4_RPWM: U4.10 (GPIO17); also elsewhere on the board
ACT_EN: R18.1, U4.31 (GPIO39)
ACT_EN5: Q4.3 (D), R23.2; also elsewhere on the board
ACT_GATE: C12.1, Q3.1 (G), R19.2, R20.1
BUS_VS: U4.15 (GPIO9); also elsewhere on the board
EN_N: Q3.3 (D), Q4.1 (G), R22.2
ESTOP_RET: J5.2, R19.1, R21.1
ESTOP_SENSE: R21.2, U4.30 (GPIO40)
ESTOP_SRC: J5.1, R18.2
GND: C12.2, C13.2, D8.1 (K), J6.2, Q3.2 (S), Q4.2 (S), R20.2, U4.22 (GND), U4.23 (GND), U4.43 (GND), U4.44 (GND); also elsewhere on the board
IMU_INT: J6.5, R24.2, U4.41 (GPIO20)
IMU_RST: J6.6, U4.42 (GPIO19)
LED_ERR: R15.1, U4.14 (GPIO46)
LED_ERR_A: D8.2 (A), R15.2
SCL: J6.3, R17.2, U4.28 (GPIO42); also elsewhere on the board
SDA: J6.4, R16.2, U4.29 (GPIO41); also elsewhere on the board
SSR1_EN: U4.40 (GPIO21); also elsewhere on the board
SSR2_EN: U4.39 (GPIO47); also elsewhere on the board
V12_SNS: U4.16 (GPIO10); also elsewhere on the board

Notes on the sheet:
ESP
ESP32-S3-DevKitC-1 in 2x22 sockets (hand-soldered). ADC1 GPIO1-10 all used (pots, IS currents, bus, 12 V). GPIO19/20 used -> program via the "UART" USB port. GPIO35-37 free (octal PSRAM on R8 variants), GPIO38/48 = on-board RGB LED.
ESTOP
Hardware E-stop -> IBT-2 enable: ACT_EN (GPIO39) runs through the NC E-stop loop to Q_A; Q_B inverts again, so EN5 (IDC pins 3/4 = R_EN/L_EN) is high only while the loop is closed AND the ESP drives ACT_EN. ESP reset / loop open -> EN5 low -> bridges off. Fit a wire bridge if no E-stop is used.
IMU
BNO085 (Adafruit 4754) on cable: 5 V, I2C @0x4A, INT -> GPIO20, RST <- GPIO19.
MECH
Mounting holes M3.
